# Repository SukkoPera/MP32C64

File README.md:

# MP32C64
MP32C64 is a simple adapter that allows connecting any audio source to the Datassette port of a Commodore VIC-20, 64, 128 or Plus/4 computer.

## Summary
With this adapter, any audio source can be used in place of the proprietary Commodore Datassette, in order to load software into a Commodore computer through the dedicated port.

It was originally developed by the Spanish C64 freak Kopsec, probably inspired by the adapter that came with [1st CD-Edition](https://www.c64-wiki.com/wiki/1st_CD-Edition_(Collection)).

As the name suggests, beside Audio CDs, MP3 files will also work, so a smartphone (provided that you have an old model with an audio jack...) or any other audio player can be used.

Another similar project, which works just as well as this one, is [DatassetteAudioAdapter](https://github.com/SukkoPera/DatassetteAudioAdapter).

PRG files can be converted to audio using the [WAV-PRG](https://wav-prg.sourceforge.io/) software suite.

> [!IMPORTANT]
> This adapter only works for playing back audio files, there is no support for recording.

## Assembly
The original adapter used 6.8k and 68k resistors, but I didn't have those values when I built the first prototype, so I used 4.7k and 47k and they worked well. Probably 10k and 100k would also work, so give these a try before buying new resistors for the purpose.

The adapter can either be built with a PJRAN1X1U01X RCA/Cinch connector or with a SJ1-3525N 3.5" headphone jack connector, according to your preference. Note that the RCA connector will point towards the back, while the headphone jack will point to the right.

## Usage
The first thing to do is to set the playback volume: start with 0 and gradually increase it until the *Signal* LED is constantly on. You can still go up a few ticks from there, experiment a bit until you have successful loads.

Second thing is motor control: you have probably noticed that the computer is able to start and stop the Datassette motor at will, but of course it cannot stop an MP3 or CD player, therefore playback control will be on you: keep an eye on the *Motor* LED and pause the playback as soon as possible whenever it goes off, then restart it when it lights up again (for the latter you don't need to rush). This is particularly important when the "FOUND XXX" screen shows up in BASIC, as if you leave the player running, it might run past the data start while the computer is still waiting to start the loading. You can also press the space bar at this point, as it will abort the wait and start the loading immediately.

Also be aware of the *NORM/INV* jumper: this should stay in the *NORM* position for the vast majority of files. In case you know you have one that was encoded with inverse polarity, or if something just doesn't load, you can try the *INV* setting.

One last thing to keep in mind is that the adapter always behaves as if the *Play* button was pressed. Therefore, if a game explicitly asks to stop the Datassette, you will have to unplug the adapter, which is not very nice, so I don't take any responsibility for anything that might happen.

## Releases
If you want to get this board produced, you are recommended to get [the latest release](https://github.com/SukkoPera/MP32C64/releases) rather than the current git version, as the latter might be under development and is not guaranteed to be working.

Every release is accompanied by its Bill Of Materials (BOM) file and any relevant notes about it, which you are recommended to read carefully.

## License
The MP32C64 documentation, including the design itself, is copyright &copy; SukkoPera 2025 and is licensed under the [Creative Commons Attribution-NonCommercial-ShareAlike 4.0 International License](https://creativecommons.org/licenses/by-nc-sa/4.0/).

This documentation is distributed *as is* and WITHOUT ANY EXPRESS OR IMPLIED WARRANTIES whatsoever with respect to its functionality, operability or use, including, without limitation, any implied warranties OF MERCHANTABILITY, SATISFACTORY QUALITY, FITNESS FOR A PARTICULAR PURPOSE or infringement. We expressly disclaim any liability whatsoever for any direct, indirect, consequential, incidental or special damages, including, without limitation, lost revenues, lost profits, losses resulting from business interruption or loss of data, regardless of the form of action or legal theory under which the liability may be asserted, even if advised of the possibility or likelihood of such damages.

## Support the Project
If you want to get some boards manufactured, you can get them from PCBWay through this link:

You get my gratitude and cheap, professionally-made and good quality PCBs, I get some credit that will help with this and [other projects](https://www.pcbway.com/project/member/shareproject/?bmbid=41100). You won't even have to worry about the various PCB options, it's all pre-configured for you!

Also, if you still have to register, [you can use this link](https://www.pcbway.com/setinvite.aspx?inviteid=41100) to get some bonus initial credit (and yield me some more).

You can also buy me a coffee if you want:

## Thanks
* Kopsec for designing the original adapter.
* [C64-Wiki](https://www.c64-wiki.com/wiki/Main_Page) for preserving the schematics and various information about the adapter.
* Kinmami for validating the design.

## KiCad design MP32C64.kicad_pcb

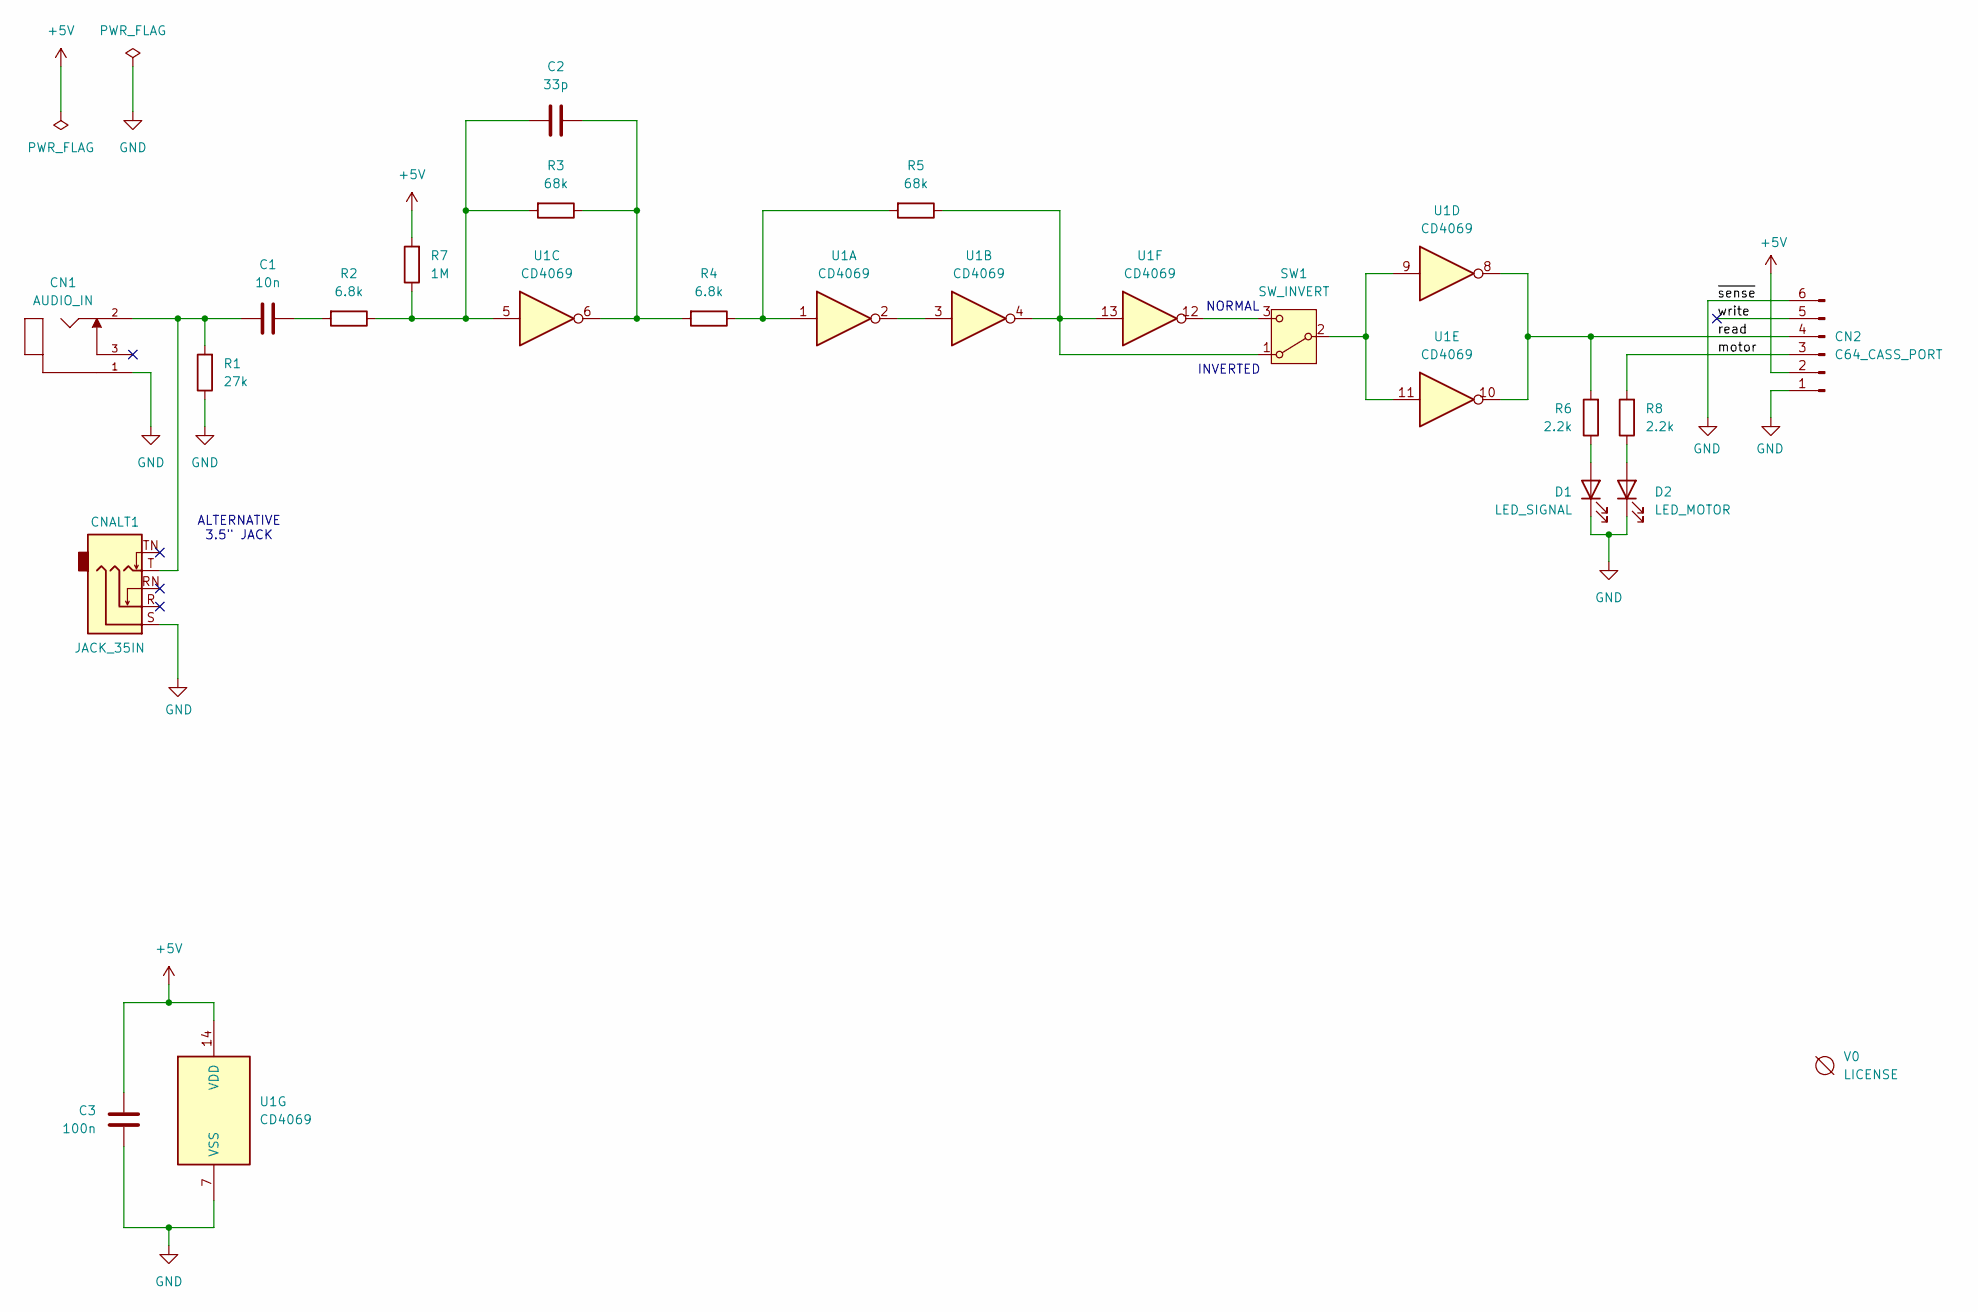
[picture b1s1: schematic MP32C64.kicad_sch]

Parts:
C1: 10n; C_Disc_D7.0mm_W2.5mm_P5.00mm
C2: 33p; C_Disc_D7.0mm_W2.5mm_P5.00mm
C3: 100n; C_Disc_D7.0mm_W2.5mm_P5.00mm
CN1: AUDIO_IN; SWITCHCRAFT_PJRAN1X1U01X
CN2: C64_CASS_PORT; C64-Cassette-Port-Female
CNALT1: JACK_35IN; AudioJack_SJ1-3525N
D1: LED_SIGNAL; LED_D3.0mm
D2: LED_MOTOR; LED_D3.0mm
R1: 27k; R_Axial_DIN0207_L6.3mm_D2.5mm_P10.16mm_Horizontal
R2, R4: 6.8k; R_Axial_DIN0207_L6.3mm_D2.5mm_P10.16mm_Horizontal
R3, R5: 68k; R_Axial_DIN0207_L6.3mm_D2.5mm_P10.16mm_Horizontal
R6, R8: 2.2k; R_Axial_DIN0207_L6.3mm_D2.5mm_P10.16mm_Horizontal
R7: 1M; R_Axial_DIN0207_L6.3mm_D2.5mm_P10.16mm_Horizontal
SW1: SW_INVERT; PinHeader_1x03_P2.54mm_Vertical
U1: CD4069; DIP-14_W7.62mm_Socket_LongPads
V0: LICENSE; cc_by_nc_sa_small

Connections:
+5V: C3.2, CN2.2, R7.2, U1.14 (VDD)
/motor: CN2.3, R8.2
/read: CN2.4, R6.2, U1.8, U1.10
/write: CN2.5
/write_1: CN2.5
GND: C3.1, CN1.1, CN2.1, CN2.6, CNALT1.S, D1.1 (K), D2.1 (K), R1.1, U1.7 (VSS)
unnamed: C1.1, CN1.2, CNALT1.T, R1.2
unnamed: C1.2, R2.2
unnamed: C2.1, R2.1, R3.2, R7.1, U1.5
unnamed: C2.2, R3.1, R4.2, U1.6
unnamed: D1.2 (A), R6.1
unnamed: D2.2 (A), R8.1
unnamed: R4.1, R5.2, U1.1
unnamed: R5.1, SW1.1 (A), U1.4, U1.13
unnamed: SW1.2 (B), U1.9, U1.11
unnamed: SW1.3 (C), U1.12
unnamed: U1.2, U1.3

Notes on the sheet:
NORMAL
INVERTED
ALTERNATIVE 3.5" JACK

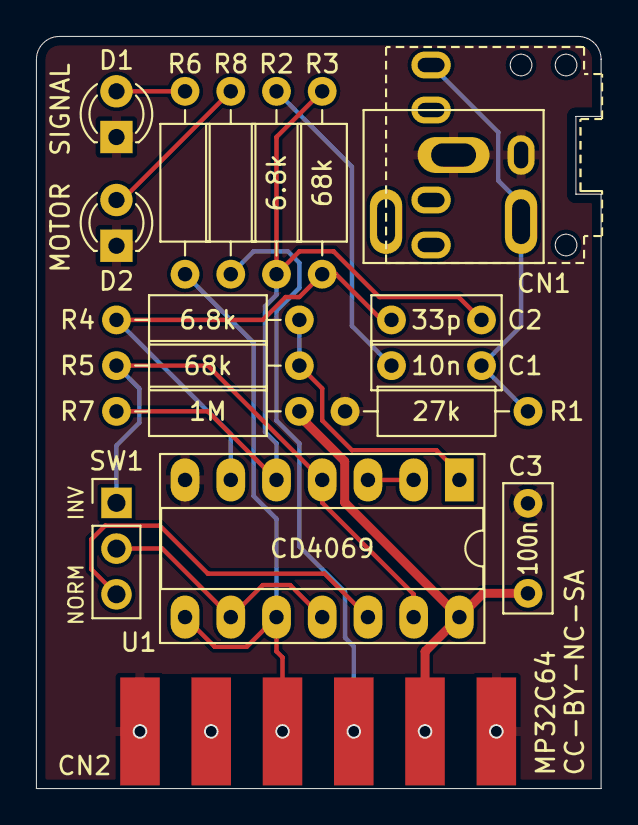
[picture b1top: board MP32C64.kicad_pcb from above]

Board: 2 copper layers, 31.4 x 41.8 mm, 19 parts (1 on the bottom side), 15 nets.

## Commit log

2025-02-06 Almost ready
2025-02-10 Add dual support for RCA/3.5" jack connector
2025-03-17 Add license, etc.
2025-03-17 Replace dual LED with 2 separate LEDs
2025-03-25 Add C2, found in some other schematics
2025-04-02 Tidy up
2025-06-30 Fix resistor values & add renders
2025-06-30 Add README
